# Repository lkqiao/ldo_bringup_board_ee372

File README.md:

# ldo_bringup_board_ee372

LDO bring up PCB for EE372.

- 20 µF / 390 mΩ RC dominant pole compensation at VOUT
- 0.1 µF cap at the NR pin for bandgap reference noise filtering
- Switch on the MD pin to toggle between high power and low power modes

## Project libraries

Both libraries are registered in the project-local `sym-lib-table` /
`fp-lib-table` under the nickname `ldo_bringup_board_ee372`, via
`${KIPRJMOD}`, so they resolve on any clone without per-machine setup.

| File | Contents |
|------|----------|
| `ldo_bringup_board_ee372.kicad_sym` | `LDO_DualMode_BGR_EE372` — 32-pin symbol + EP |
| `ldo_bringup_board_ee372.pretty/` | `QFN-32-1EP_7x7mm_P0.65mm_EP5.1x5.1mm_QuikPak` |

### Package

Quik-Pak **QP-QFN32-7MM-.65MM**, open-cavity QFN-32, rev A2. The numbers
come from the EE372B PCB Design Guidelines (Fall 2026, section 2), the
Quik-Pak mechanical drawing `QP-QFN7X7-32-650 PACKAGE.pdf` and the bonding
drawing `QP-QFN7X7-32-650 BONDING.dwg`.

| Parameter | Value | Source |
|---|---|---|
| Body | 7.000 x 7.000 mm, 0.800 tall | guidelines 2.1, package drawing |
| Leads | 32 (8/side), pitch 0.650 mm | guidelines 2.1, package drawing |
| Lead width x length | 0.300 x 0.380 mm | package drawing, bottom view |
| Lead-centre span per side | 4.550 mm | package drawing, bottom view |
| Exposed paddle (bottom) | 5.100 x 5.100 mm | package drawing, bottom view |
| Die attach surface (in the cavity) | 5.300 x 5.300 mm | bonding drawing note 3; not the land size |
| Pin-1 ID | 0.400 x 45 deg chamfer | package drawing, top view |

### Footprint

`QFN-32-1EP_7x7mm_P0.65mm_EP5.1x5.1mm_QuikPak`, checked against every
requirement in guidelines section 2.2.

| Pad size | Pitch | EP land | Courtyard |
|---|---|---|---|
| 0.30 x 0.85 mm | 0.65 mm | 5.10 x 5.10 mm | 8.26 x 8.26 mm |

- Lands extend 0.375 mm past the body edge and sit 0.475 mm from the EP land.
- 9 thermal vias, 0.3 mm drill, numbered 33 with the EP. They are tented on
  both sides because the EP has no full mask opening. Instead, 16 mask windows
  sit exactly over the 16 paste windows.
- EP paste is a 4x4 window pane at 52.5% coverage.
- Pin 1 is marked on silkscreen with a dot and a 0.4 mm chamfered corner.
- The 3D model is KiCad's stock `QFN-32-1EP_7x7mm_P0.65mm_EP5.46x5.46mm.step`,
  0.9 mm tall with a closed top. It is only for renders.

### Pinout

From the die pad map. Package pin 1 = the first pad down the **left** side,
i.e. the die orientation mark aligned to the package `PIN #1 ID`. Numbering
then runs CCW: left T→B (1-8), bottom L→R (9-16), right B→T (17-24),
top R→L (25-32). Pin 33 is the exposed pad.

| | | | |
|---|---|---|---|
| 1 VSS | 9 VDD | 17 VSS | 25 VDD |
| 2 VSS | 10 VSS | 18 VSS | 26 VDD |
| 3 VSS | 11 VSS | 19 VSS | 27 VDD |
| 4 VDD | 12 VSS | 20 VSS | 28 VSS |
| 5 IBIAS | 13 VSS | 21 VOUT | 29 MD |
| 6 VSS | 14 VSS | 22 VOUT | 30 NR |
| 7 VSS | 15 VSS | 23 VSS | 31 VSS |
| 8 VDD | 16 VDD | 24 VDD | 32 VDD |

Census: 18 × VSS, 9 × VDD, 2 × VOUT, 1 × MD, 1 × NR, 1 × IBIAS = 32.

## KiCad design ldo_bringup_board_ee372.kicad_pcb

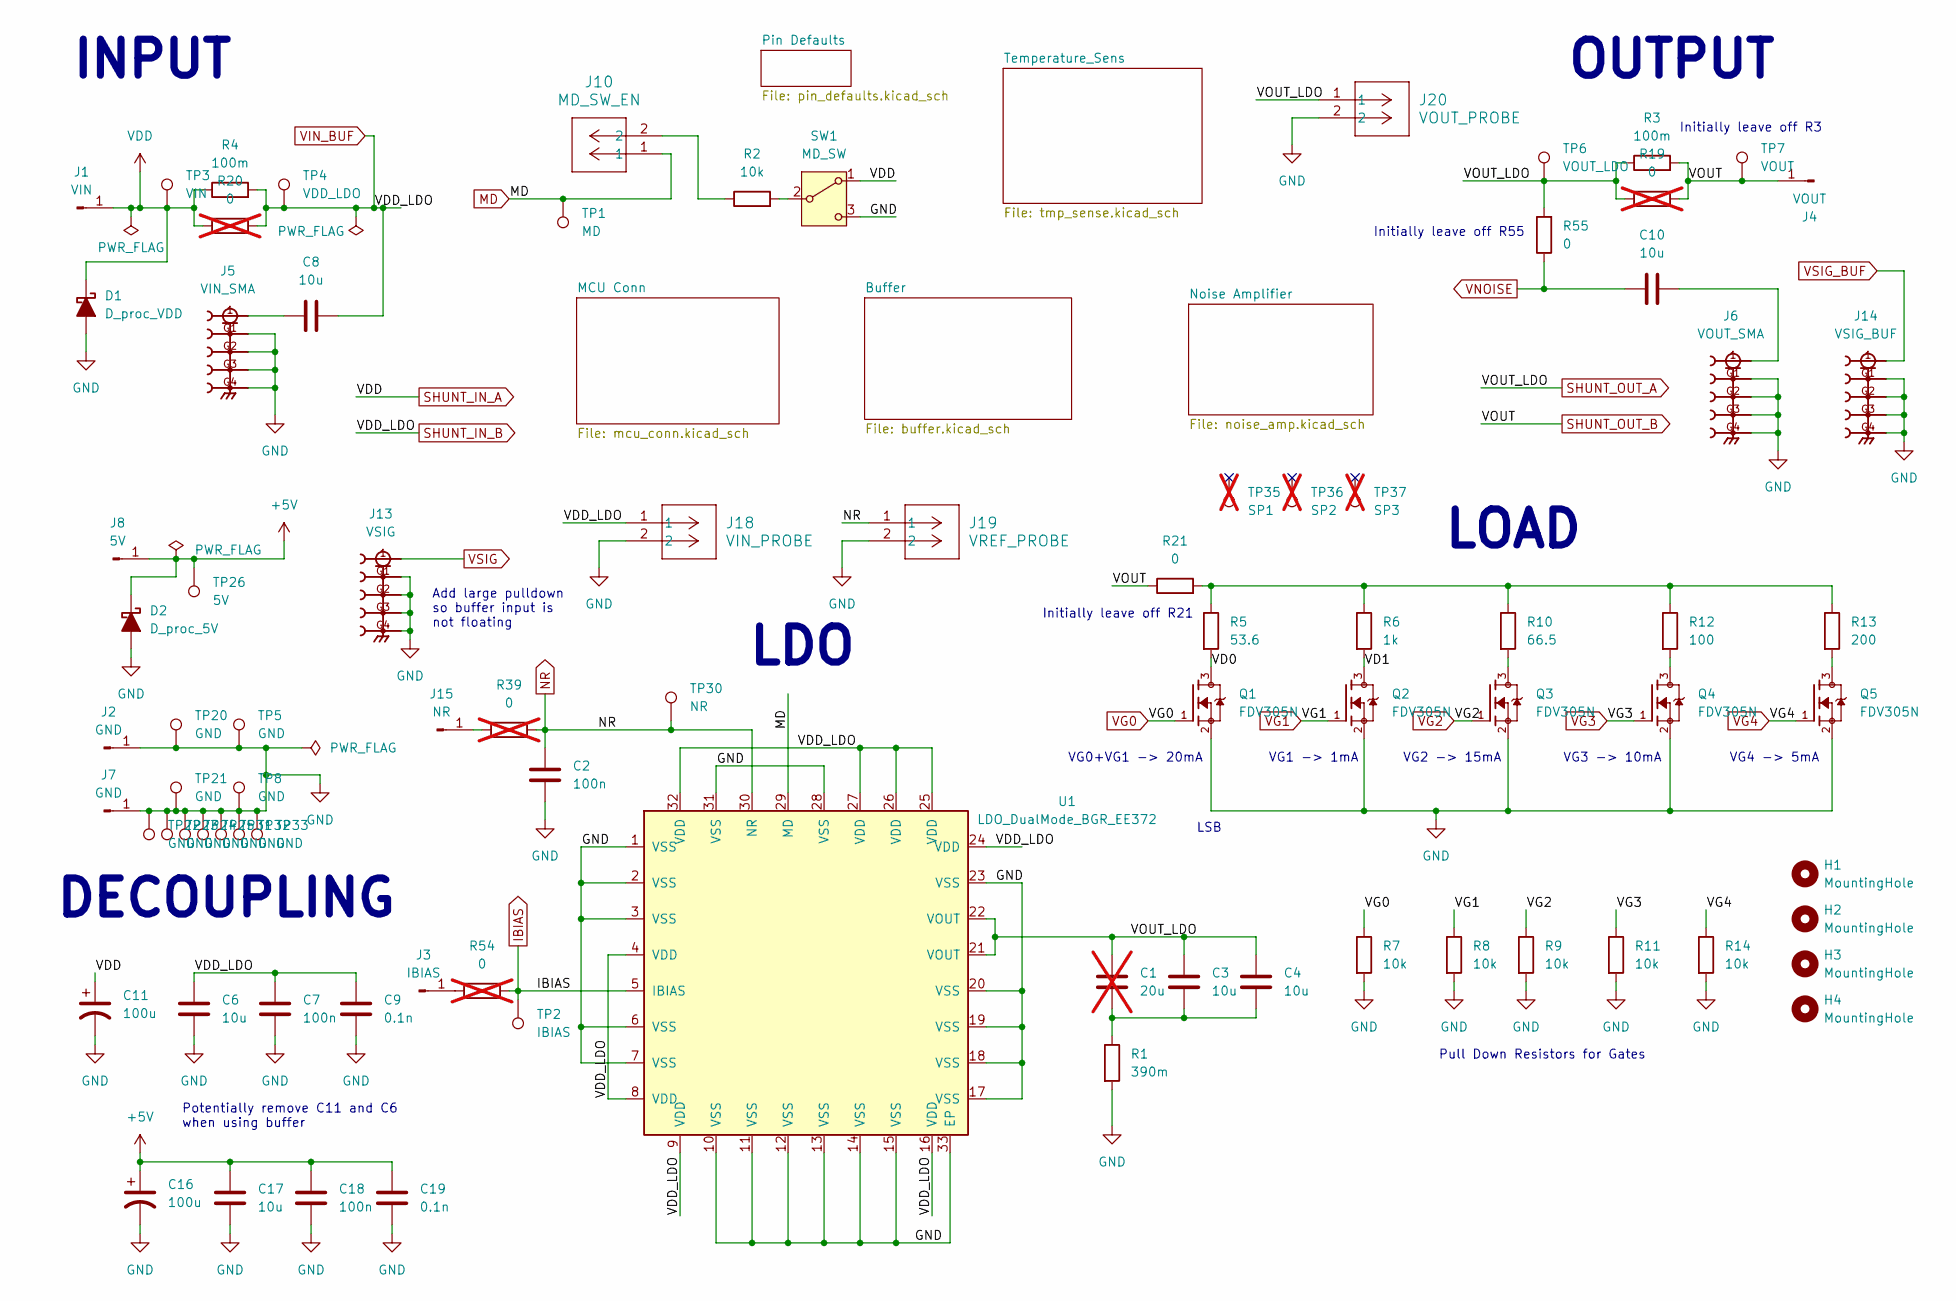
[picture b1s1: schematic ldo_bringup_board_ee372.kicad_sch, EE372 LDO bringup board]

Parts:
C1: 20u; C_1812_4532Metric_Pad1.57x3.40mm_HandSolder; Manufacturer Part Number C1812C206K3RLCTU; not fitted
C2, C7, C18: 100n; C_0805_2012Metric_Pad1.18x1.45mm_HandSolder; Manufacturer Part Number CL21B104KBCNNNC
C3, C4: 10u; C_1206_3216Metric_Pad1.33x1.80mm_HandSolder; Manufacturer Part Number C1206C106J3RACAUTO
C6, C8, C10, C17: 10u; C_1206_3216Metric_Pad1.33x1.80mm_HandSolder; Manufacturer Part Number GRM319R61E106KA12D
C9, C19: 0.1n; C_0805_2012Metric_Pad1.18x1.45mm_HandSolder; Manufacturer Part Number CL21C101JBANNNC
C11, C16: 100u; CP_Radial_D6.3mm_P2.50mm; Manufacturer Part Number EEU-FC1E101S
D1: D_proc_VDD; D_SMA_Handsoldering; Manufacturer Part Number B120-13-F
D2: D_proc_5V; D_SMA_Handsoldering; Manufacturer Part Number B120-13-F
H1, H2, H3, H4: MountingHole; MountingHole_3.2mm_M3
J1: VIN; CalTest_CT3151SP; Manufacturer Part Number CT3151SP-2
J2, J7: GND; CalTest_CT3151SP; Manufacturer Part Number CT3151SP-0
J3: IBIAS; CalTest_CT3151SP; Manufacturer Part Number CT3151SP-9
J4: VOUT; CalTest_CT3151SP; Manufacturer Part Number CT3151SP-4
J5: VIN_SMA; SMA_Samtec_SMA-J-P-H-ST-EM1_EdgeMount_G; Manufacturer Part Number SMA-J-P-H-ST-EM1
J6: VOUT_SMA; SMA_Samtec_SMA-J-P-H-ST-EM1_EdgeMount_G; Manufacturer Part Number SMA-J-P-H-ST-EM1
J8: 5V; CalTest_CT3151SP; Manufacturer Part Number CT3151SP-2
J10: MD_SW_EN; CONN_PxC02S_SUL; Manufacturer Part Number PEC02SAAN
J13: VSIG; SMA_Samtec_SMA-J-P-H-ST-EM1_EdgeMount_G; Manufacturer Part Number SMA-J-P-H-ST-EM1
J14: VSIG_BUF; SMA_Samtec_SMA-J-P-H-ST-EM1_EdgeMount_G; Manufacturer Part Number SMA-J-P-H-ST-EM1
J15: NR; CalTest_CT3151SP; Manufacturer Part Number CT3151SP-2
J18: VIN_PROBE; CONN_PxC02S_SUL; Manufacturer Part Number PEC02SAAN
J19: VREF_PROBE; CONN_PxC02S_SUL; Manufacturer Part Number PEC02SAAN
J20: VOUT_PROBE; CONN_PxC02S_SUL; Manufacturer Part Number PEC02SAAN
Q1, Q2, Q3, Q4, Q5: FDV305N; SOT95P240X111-3N; Manufacturer Part Number FDV305N
R1: 390m; R_0805_2012Metric_Pad1.20x1.40mm_HandSolder; Manufacturer Part Number ERJ-6BQFR39V
R2, R7, R8, R9, R11, R14: 10k; R_0805_2012Metric_Pad1.20x1.40mm_HandSolder; Manufacturer Part Number RC0805FR-0710KL
R3, R4: 100m; R_0805_2012Metric_Pad1.20x1.40mm_HandSolder; Manufacturer Part Number ERJ-6DSFR10V
R5: 53.6; R_0805_2012Metric_Pad1.20x1.40mm_HandSolder; Manufacturer Part Number RC0805FR-0753R6L
R6: 1k; R_0805_2012Metric_Pad1.20x1.40mm_HandSolder; Manufacturer Part Number RC0805FR-071KL
R10: 66.5; R_0805_2012Metric_Pad1.20x1.40mm_HandSolder; Manufacturer Part Number RC0805FR-0766R5L
R12: 100; R_0805_2012Metric_Pad1.20x1.40mm_HandSolder; Manufacturer Part Number RC0805FR-07100RL
R13: 200; R_0805_2012Metric_Pad1.20x1.40mm_HandSolder; Manufacturer Part Number RC0805FR-07200RL
R19, R20, R39, R54: 0; R_0805_2012Metric_Pad1.20x1.40mm_HandSolder; Manufacturer Part Number CRCW08050000Z0EAHP; not fitted
R21, R55: 0; R_0805_2012Metric_Pad1.20x1.40mm_HandSolder; Manufacturer Part Number CRCW08050000Z0EAHP
SW1: MD_SW; SW_SPDT_CK_JS102011SAQN; Manufacturer Part Number JS102011SAQN
TP1: MD; TestPoint_Keystone_5005-5009_Compact; Manufacturer Part Number 5005
TP2: IBIAS; TestPoint_Keystone_5005-5009_Compact; Manufacturer Part Number 5005
TP3: VIN; TestPoint_Keystone_5005-5009_Compact; Manufacturer Part Number 5005
TP4: VDD_LDO; TestPoint_Keystone_5005-5009_Compact; Manufacturer Part Number 5005
TP5, TP8, TP20, TP21, TP22, TP23, TP24, TP25, TP31, TP32, TP33: GND; TestPoint_Keystone_5005-5009_Compact; Manufacturer Part Number 5006
TP6: VOUT_LDO; TestPoint_Keystone_5005-5009_Compact; Manufacturer Part Number 5005
TP7: VOUT; TestPoint_Keystone_5005-5009_Compact; Manufacturer Part Number 5005
TP26: 5V; TestPoint_Keystone_5005-5009_Compact; Manufacturer Part Number 5005
TP30: NR; TestPoint_Keystone_5005-5009_Compact; Manufacturer Part Number 5005
TP35: SP1; TestPoint_Keystone_5005-5009_Compact; Manufacturer Part Number 5006; not fitted
TP36: SP2; TestPoint_Keystone_5005-5009_Compact; Manufacturer Part Number 5006; not fitted
TP37: SP3; TestPoint_Keystone_5005-5009_Compact; Manufacturer Part Number 5006; not fitted
U1: LDO_DualMode_BGR_EE372; QFN-32-1EP_7x7mm_P0.65mm_EP5.1x5.1mm_QuikPak

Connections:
+5V: C16.1, C17.1, C18.1, C19.1, D2.1 (K), J8.1 (Pin_1_1), TP26.1 (1_1); also elsewhere on the board
/VD0: Q1.3, R5.2
/VD1: Q2.3, R6.2
GND: C2.2, C6.2, C7.2, C9.2, C11.2, C16.2, C17.2, C18.2, C19.2, D1.2 (A), D2.2 (A), J2.1 (Pin_1_1), J5.G1, J5.G2, J5.G3, J5.G4, J6.G1, J6.G2, J6.G3, J6.G4, J7.1 (Pin_1_1), J13.G1, J13.G2, J13.G3, J13.G4, J14.G1, J14.G2, J14.G3, J14.G4, J18.2, J19.2, J20.2, Q1.2, Q2.2, Q3.2, Q4.2, Q5.2, R1.2, R7.2, R8.2, R9.2, R11.2, R14.2, SW1.3 (C), TP5.1 (1_1), TP8.1 (1_1), TP20.1 (1_1), TP21.1 (1_1), TP22.1 (1_1), TP23.1 (1_1), TP24.1 (1_1), TP25.1 (1_1), TP31.1 (1_1), TP32.1 (1_1), TP33.1 (1_1), U1.1 (VSS), U1.2 (VSS), U1.3 (VSS), U1.6 (VSS), U1.7 (VSS), U1.10 (VSS), U1.11 (VSS), U1.12 (VSS), U1.13 (VSS), U1.14 (VSS), U1.15 (VSS), U1.17 (VSS), U1.18 (VSS), U1.19 (VSS), U1.20 (VSS), U1.23 (VSS), U1.28 (VSS), U1.31 (VSS), U1.33 (EP); also elsewhere on the board
IBIAS: R54.2, TP2.1 (1_1), U1.5 (IBIAS); also elsewhere on the board
MD: J10.1, TP1.1 (1_1), U1.29 (MD); also elsewhere on the board
NR: C2.1, J19.1, R39.2, TP30.1 (1_1), U1.30 (NR); also elsewhere on the board
unnamed: C1.2, C3.2, C4.2, R1.1
unnamed: C8.1, J5.1
unnamed: C10.2, J6.1
unnamed: J3.1 (Pin_1_1), R54.1
unnamed: J10.2, R2.1
unnamed: J15.1 (Pin_1_1), R39.1
unnamed: Q3.3, R10.2
unnamed: Q4.3, R12.2
unnamed: Q5.3, R13.2
unnamed: R5.1, R6.1, R10.1, R12.1, R13.1, R21.2
unnamed: R2.2, SW1.2 (B)
SHUNT_IN_A: C11.1, D1.1 (K), J1.1 (Pin_1_1), R4.1, R20.1, SW1.1 (A), TP3.1 (1_1); also elsewhere on the board
SHUNT_IN_B: C6.1, C7.1, C8.2, C9.1, J18.1, R4.2, R20.2, TP4.1 (1_1), U1.4 (VDD), U1.8 (VDD), U1.9 (VDD), U1.16 (VDD), U1.24 (VDD), U1.25 (VDD), U1.26 (VDD), U1.27 (VDD), U1.32 (VDD); also elsewhere on the board
SHUNT_OUT_A: C1.1, C3.1, C4.1, J20.1, R3.1, R19.1, R55.2, TP6.1 (1_1), U1.21 (VOUT), U1.22 (VOUT); also elsewhere on the board
SHUNT_OUT_B: J4.1 (Pin_1_1), R3.2, R19.2, R21.1, TP7.1 (1_1); also elsewhere on the board
VG0: Q1.1, R7.1; also elsewhere on the board
VG1: Q2.1, R8.1; also elsewhere on the board
VG2: Q3.1, R9.1; also elsewhere on the board
VG3: Q4.1, R11.1; also elsewhere on the board
VG4: Q5.1, R14.1; also elsewhere on the board
VNOISE: C10.1, R55.1; also elsewhere on the board
VSIG: J13.1; also elsewhere on the board
VSIG_BUF: J14.1; also elsewhere on the board

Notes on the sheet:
OUTPUT
Potentially remove C11 and C6 when using buffer
Initially leave off R3
VG0+VG1 -> 20mA
VG3 -> 10mA
LSB
Add large pulldown so buffer input is not floating
Initially leave off R55
Pull Down Resistors for Gates
VG4 -> 5mA
LOAD
VG2 -> 15mA
DECOUPLING
Initially leave off R21
LDO
VG1 -> 1mA
INPUT

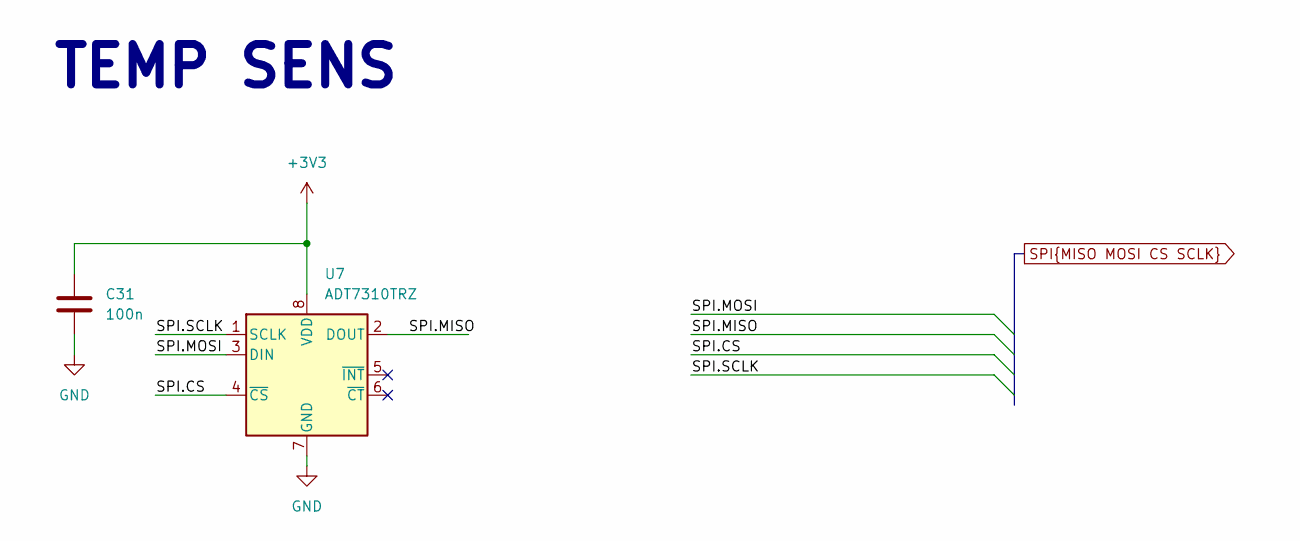
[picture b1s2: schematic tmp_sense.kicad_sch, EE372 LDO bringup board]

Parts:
C31: 100n; C_0805_2012Metric_Pad1.18x1.45mm_HandSolder; Manufacturer Part Number CL21B104KBCNNNC
U7: ADT7310TRZ; SOIC-8_3.9x4.9mm_P1.27mm; Manufacturer Part Number ADT7310TRZ

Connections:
+3V3: C31.1, U7.8 (VDD); also elsewhere on the board
GND: C31.2, U7.7 (GND); also elsewhere on the board
SPI.CS: U7.4 (~CS); also elsewhere on the board
SPI.MISO: U7.2 (DOUT); also elsewhere on the board
SPI.MOSI: U7.3 (DIN); also elsewhere on the board
SPI.SCLK: U7.1 (SCLK); also elsewhere on the board

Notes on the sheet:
TEMP SENS

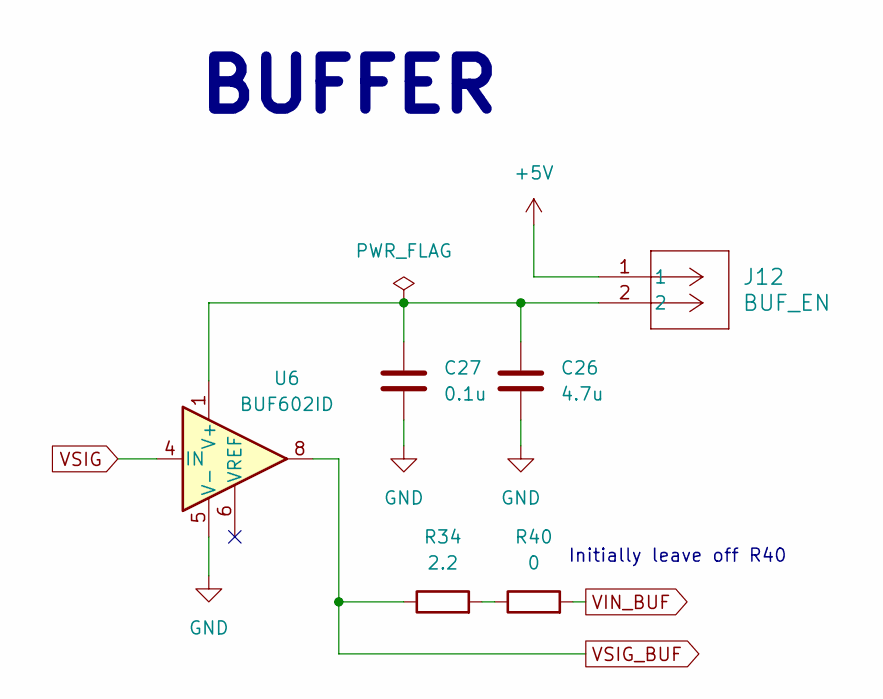
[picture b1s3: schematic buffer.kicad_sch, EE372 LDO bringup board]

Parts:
C26: 4.7u; C_0805_2012Metric_Pad1.18x1.45mm_HandSolder; Manufacturer Part Number CL21B475KAFNNNE
C27: 0.1u; C_0805_2012Metric_Pad1.18x1.45mm_HandSolder; Manufacturer Part Number CL21B104KBCNNNC
J12: BUF_EN; CONN_PxC02S_SUL; Manufacturer Part Number PEC02SAAN
R34: 2.2; R_0603_1608Metric_Pad0.98x0.95mm_HandSolder; Manufacturer Part Number ERJ-3RQF2R2V
R40: 0; R_0603_1608Metric_Pad0.98x0.95mm_HandSolder; Manufacturer Part Number CRCW06030000Z0EAHP
U6: BUF602ID; SOIC-8_3.9x4.9mm_P1.27mm; Manufacturer Part Number BUF602ID

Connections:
+5V: J12.1; also elsewhere on the board
GND: C26.1, C27.1, U6.5 (V-); also elsewhere on the board
unnamed: R34.2, R40.1
unnamed: C26.2, C27.2, J12.2, U6.1 (V+)
SHUNT_IN_B: R40.2; also elsewhere on the board
VSIG: U6.4 (IN); also elsewhere on the board
VSIG_BUF: R34.1, U6.8; also elsewhere on the board

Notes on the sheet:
Initially leave off R40
BUFFER

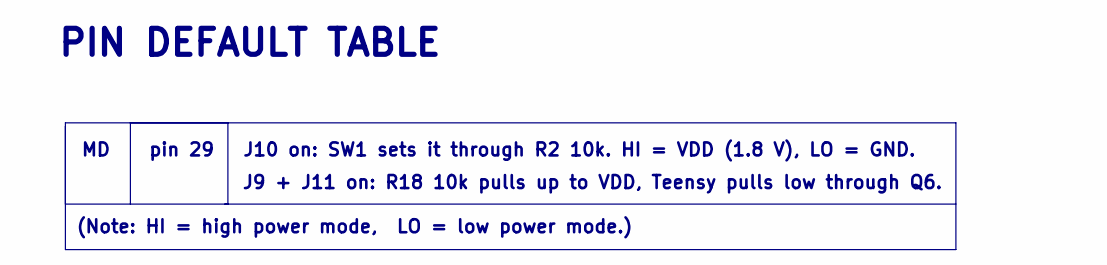
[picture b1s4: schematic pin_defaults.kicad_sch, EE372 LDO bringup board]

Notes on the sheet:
J9 + J11 on: R18 10k pulls up to VDD, Teensy pulls low through Q6.
(Note: HI = high power mode, LO = low power mode.)
PIN DEFAULT TABLE
MD pin 29 J10 on: SW1 sets it through R2 10k. HI = VDD (1.8 V), LO = GND.

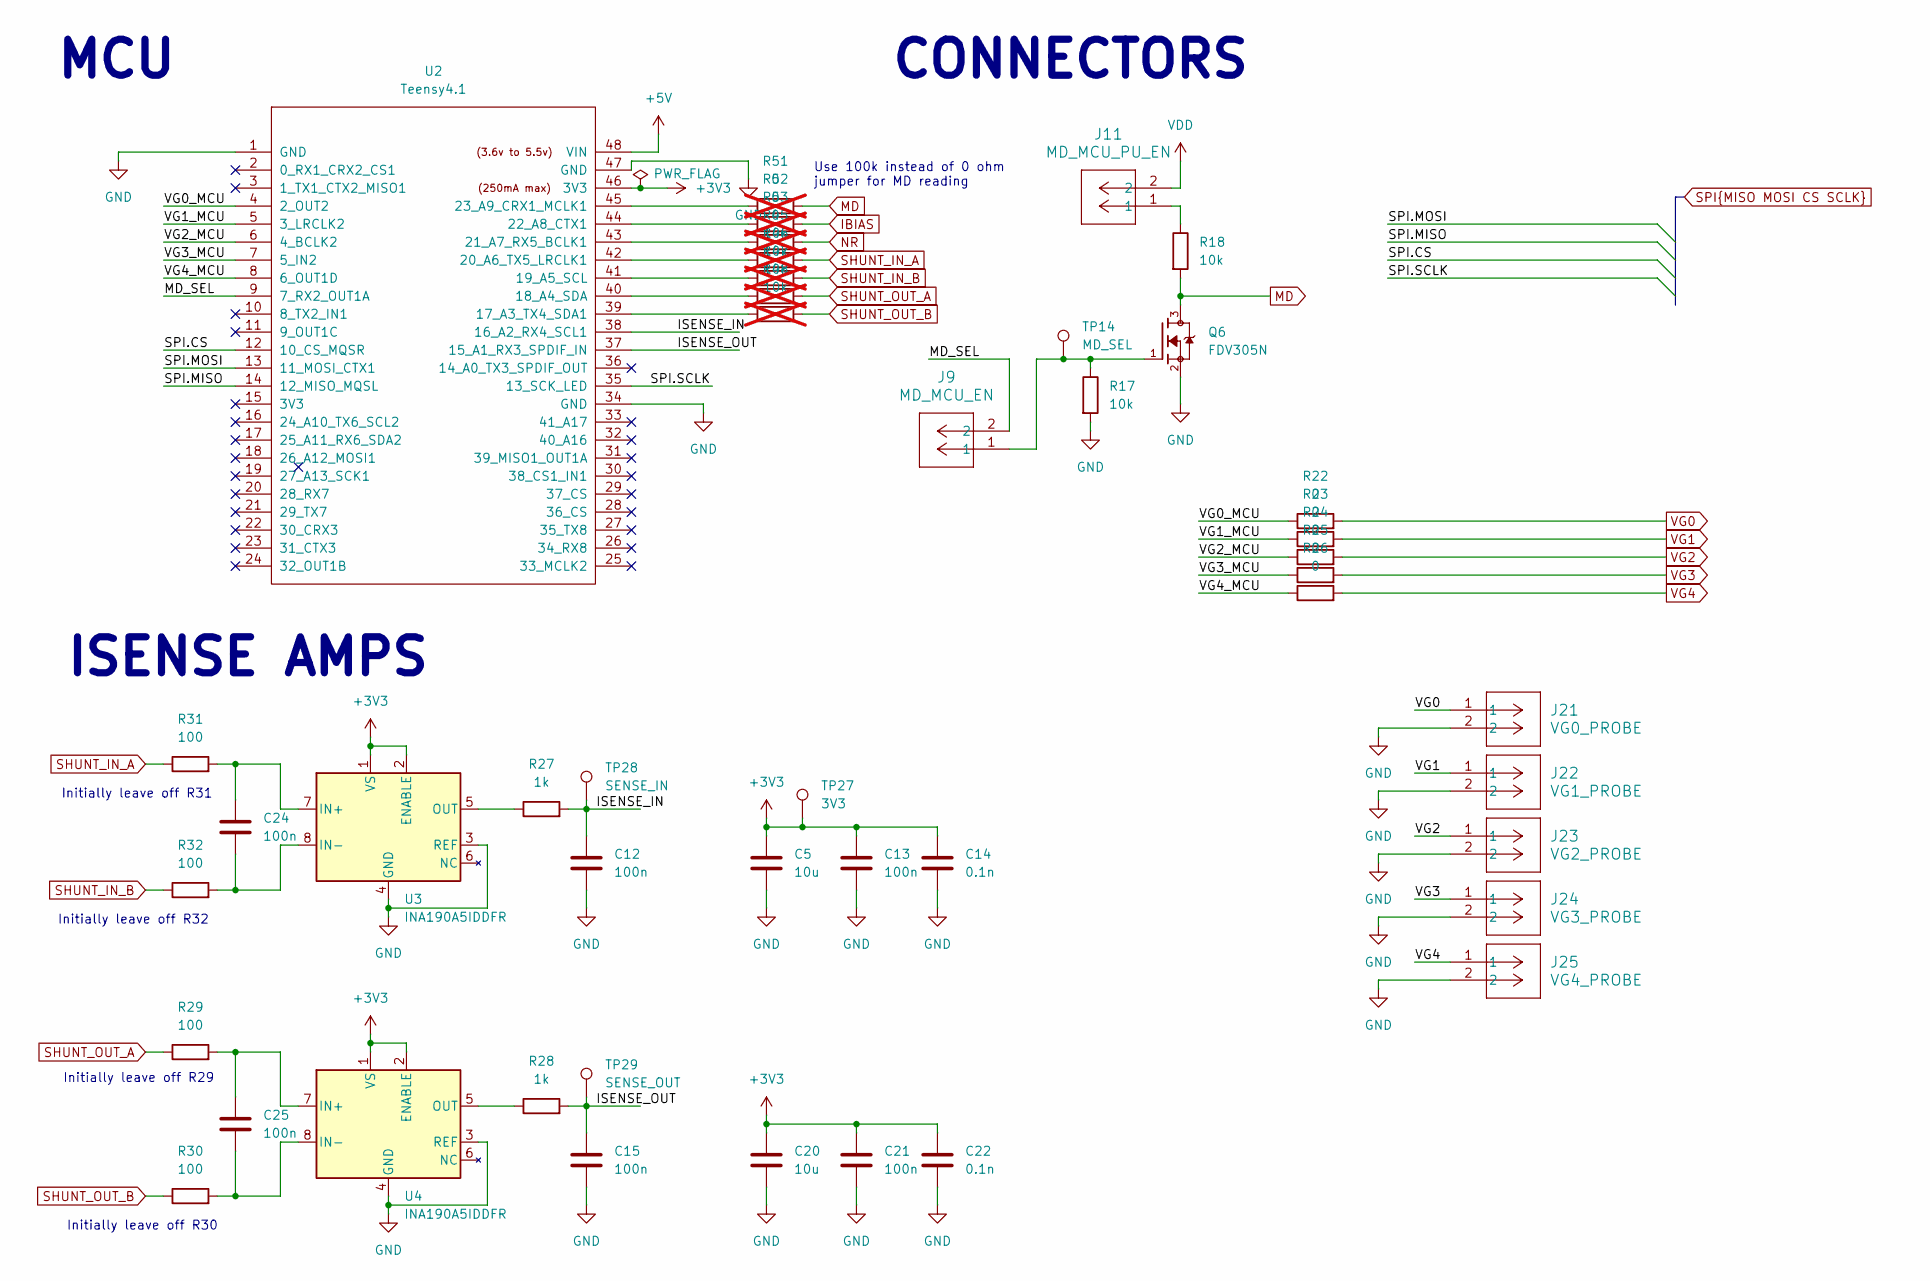
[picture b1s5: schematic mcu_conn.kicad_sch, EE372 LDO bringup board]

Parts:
C5, C20: 10u; C_1206_3216Metric_Pad1.33x1.80mm_HandSolder; Manufacturer Part Number GRM319R61E106KA12D
C12, C13, C15, C21, C24, C25: 100n; C_0805_2012Metric_Pad1.18x1.45mm_HandSolder; Manufacturer Part Number CL21B104KBCNNNC
C14, C22: 0.1n; C_0805_2012Metric_Pad1.18x1.45mm_HandSolder; Manufacturer Part Number CL21C101JBANNNC
J9: MD_MCU_EN; CONN_PxC02S_SUL; Manufacturer Part Number PEC02SAAN
J11: MD_MCU_PU_EN; CONN_PxC02S_SUL; Manufacturer Part Number PEC02SAAN
J21: VG0_PROBE; CONN_PxC02S_SUL; Manufacturer Part Number PEC02SAAN
J22: VG1_PROBE; CONN_PxC02S_SUL; Manufacturer Part Number PEC02SAAN
J23: VG2_PROBE; CONN_PxC02S_SUL; Manufacturer Part Number PEC02SAAN
J24: VG3_PROBE; CONN_PxC02S_SUL; Manufacturer Part Number PEC02SAAN
J25: VG4_PROBE; CONN_PxC02S_SUL; Manufacturer Part Number PEC02SAAN
Q6: FDV305N; SOT95P240X111-3N; Manufacturer Part Number FDV305N
R17, R18: 10k; R_0603_1608Metric_Pad0.98x0.95mm_HandSolder; Manufacturer Part Number RC0603FR-0710KL
R22, R23, R24, R25, R26: 0; R_0603_1608Metric_Pad0.98x0.95mm_HandSolder; Manufacturer Part Number CRCW06030000Z0EAHP
R27, R28: 1k; R_0603_1608Metric_Pad0.98x0.95mm_HandSolder; Manufacturer Part Number RC0603FR-071KL
R29, R30, R31, R32: 100; R_0603_1608Metric_Pad0.98x0.95mm_HandSolder; Manufacturer Part Number ERJ-3EKF1000V
R45, R46, R47, R48: 10k; R_0805_2012Metric_Pad1.20x1.40mm_HandSolder; Manufacturer Part Number RC0805FR-0710KL; not fitted
R51, R52, R53: 0; R_0603_1608Metric_Pad0.98x0.95mm_HandSolder; Manufacturer Part Number CRCW06030000Z0EAHP; not fitted
TP14: MD_SEL; TestPoint_Keystone_5005-5009_Compact; Manufacturer Part Number 5005
TP27: 3V3; TestPoint_Keystone_5005-5009_Compact; Manufacturer Part Number 5005
TP28: SENSE_IN; TestPoint_Keystone_5005-5009_Compact; Manufacturer Part Number 5005
TP29: SENSE_OUT; TestPoint_Keystone_5005-5009_Compact; Manufacturer Part Number 5005
U2: Teensy4.1; Teensy41_Sockets
U3, U4: INA190A5IDDFR; TSOT-23-8_HandSoldering; Manufacturer Part Number INA190A5IDDFR

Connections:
+3V3: C5.1, C13.1, C14.1, C20.1, C21.1, C22.1, TP27.1 (1_1), U2.46 (3V3), U3.1 (VS), U3.2 (ENABLE), U4.1 (VS), U4.2 (ENABLE); also elsewhere on the board
+5V: U2.48 (VIN); also elsewhere on the board
/MCU Conn/ISENSE_IN: C12.1, R27.2, TP28.1 (1_1), U2.38 (16_A2_RX4_SCL1)
/MCU Conn/ISENSE_OUT: C15.1, R28.2, TP29.1 (1_1), U2.37 (15_A1_RX3_SPDIF_IN)
/MCU Conn/MD_SEL: J9.2, U2.9 (7_RX2_OUT1A)
/MCU Conn/VG0_MCU: R22.1, U2.4 (2_OUT2)
/MCU Conn/VG1_MCU: R23.1, U2.5 (3_LRCLK2)
/MCU Conn/VG2_MCU: R24.1, U2.6 (4_BCLK2)
/MCU Conn/VG3_MCU: R25.1, U2.7 (5_IN2)
/MCU Conn/VG4_MCU: R26.1, U2.8 (6_OUT1D)
GND: C5.2, C12.2, C13.2, C14.2, C15.2, C20.2, C21.2, C22.2, J21.2, J22.2, J23.2, J24.2, J25.2, Q6.2, R17.2, U2.1 (GND), U2.34 (GND), U2.47 (GND), U3.3 (REF), U3.4 (GND), U4.3 (REF), U4.4 (GND); also elsewhere on the board
IBIAS: R52.2; also elsewhere on the board
MD: Q6.3, R18.2, R51.2; also elsewhere on the board
NR: R53.2; also elsewhere on the board
unnamed: J9.1, Q6.1, R17.1, TP14.1 (1_1)
unnamed: J11.1, R18.1
unnamed: R48.1, U2.39 (17_A3_TX4_SDA1)
unnamed: R47.1, U2.40 (18_A4_SDA)
unnamed: R46.1, U2.41 (19_A5_SCL)
unnamed: R45.1, U2.42 (20_A6_TX5_LRCLK1)
unnamed: R53.1, U2.43 (21_A7_RX5_BCLK1)
unnamed: R52.1, U2.44 (22_A8_CTX1)
unnamed: R51.1, U2.45 (23_A9_CRX1_MCLK1)
unnamed: C24.1, R31.2, U3.7 (IN+)
unnamed: C24.2, R32.2, U3.8 (IN-)
unnamed: R27.1, U3.5 (OUT)
unnamed: C25.1, R29.2, U4.7 (IN+)
unnamed: C25.2, R30.2, U4.8 (IN-)
unnamed: R28.1, U4.5 (OUT)
SHUNT_IN_A: J11.2, R31.1, R45.2; also elsewhere on the board
SHUNT_IN_B: R32.1, R46.2; also elsewhere on the board
SHUNT_OUT_A: R29.1, R47.2; also elsewhere on the board
SHUNT_OUT_B: R30.1, R48.2; also elsewhere on the board
SPI.CS: U2.12 (10_CS_MQSR); also elsewhere on the board
SPI.MISO: U2.14 (12_MISO_MQSL); also elsewhere on the board
SPI.MOSI: U2.13 (11_MOSI_CTX1); also elsewhere on the board
SPI.SCLK: U2.35 (13_SCK_LED); also elsewhere on the board
VG0: J21.1, R22.2; also elsewhere on the board
VG1: J22.1, R23.2; also elsewhere on the board
VG2: J23.1, R24.2; also elsewhere on the board
VG3: J24.1, R25.2; also elsewhere on the board
VG4: J25.1, R26.2; also elsewhere on the board

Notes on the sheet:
CONNECTORS
MCU
Use 100k instead of 0 ohm jumper for MD reading
Initially leave off R29
ISENSE AMPS
Initially leave off R32
Initially leave off R30
Initially leave off R31

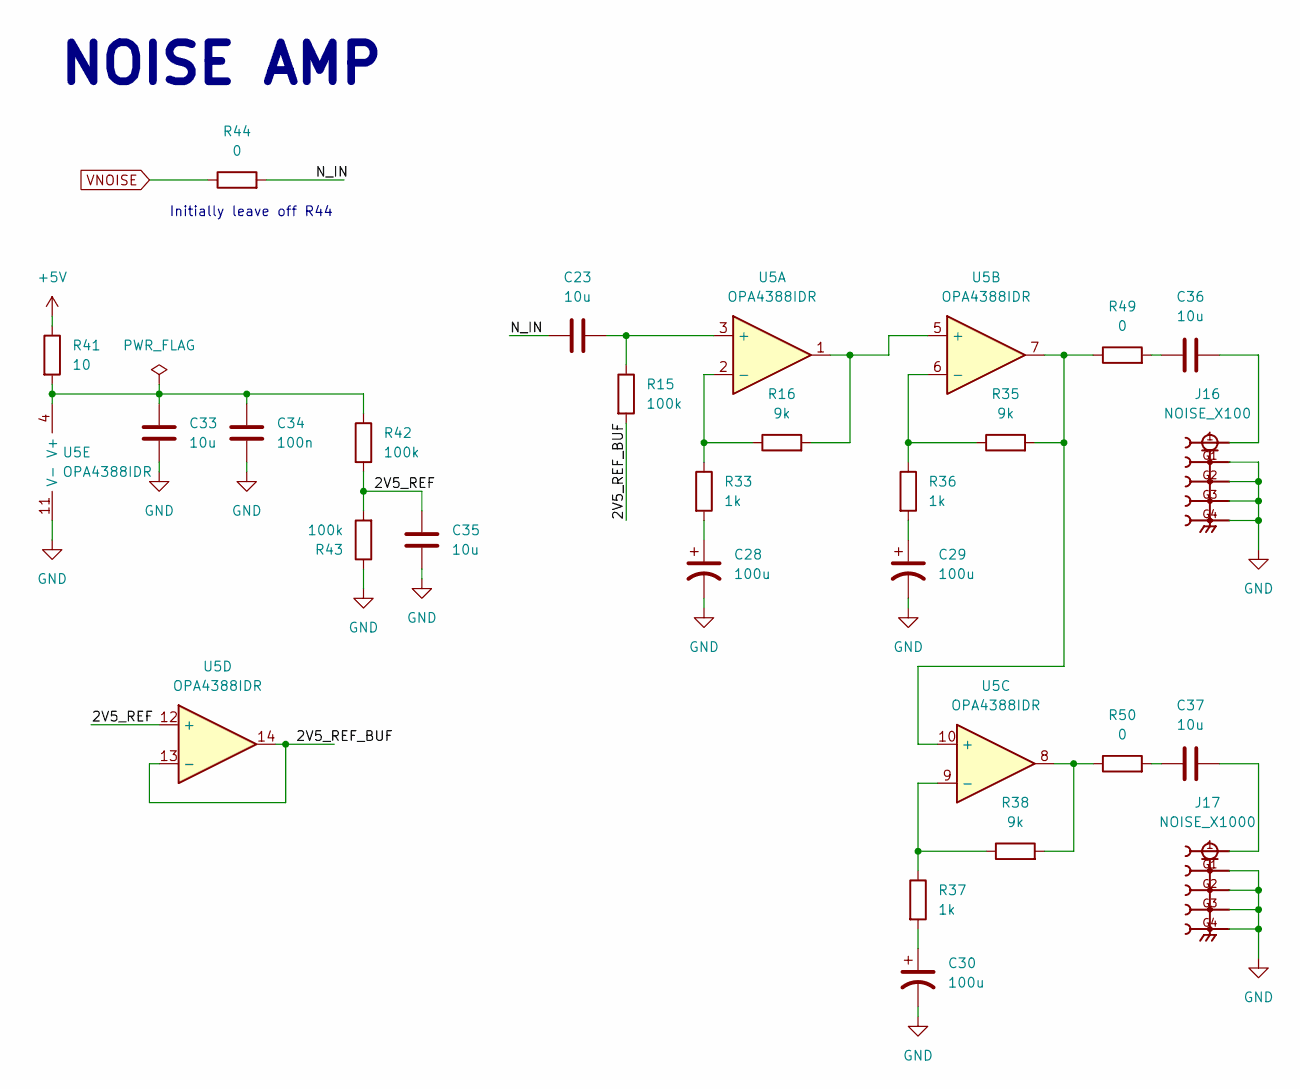
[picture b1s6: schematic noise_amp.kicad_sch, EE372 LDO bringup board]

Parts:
C23, C33, C35, C36, C37: 10u; C_1206_3216Metric_Pad1.33x1.80mm_HandSolder; Manufacturer Part Number GRM319R61E106KA12D
C28, C29, C30: 100u; CP_Radial_D6.3mm_P2.50mm; Manufacturer Part Number EEU-FC1E101S
C34: 100n; C_0805_2012Metric_Pad1.18x1.45mm_HandSolder; Manufacturer Part Number CL21B104KBCNNNC
J16: NOISE_X100; SMA_Samtec_SMA-J-P-H-ST-EM1_EdgeMount_G; Manufacturer Part Number SMA-J-P-H-ST-EM1
J17: NOISE_X1000; SMA_Samtec_SMA-J-P-H-ST-EM1_EdgeMount_G; Manufacturer Part Number SMA-J-P-H-ST-EM1
R15, R42, R43: 100k; R_0603_1608Metric_Pad0.98x0.95mm_HandSolder; Manufacturer Part Number RC0603FR-07100KL
R16, R35, R38: 9k; R_0805_2012Metric_Pad1.20x1.40mm_HandSolder; Manufacturer Part Number RT0805BRE079KL
R33, R36, R37: 1k; R_0603_1608Metric_Pad0.98x0.95mm_HandSolder; Manufacturer Part Number RC0603FR-071KL
R41: 10; R_0603_1608Metric_Pad0.98x0.95mm_HandSolder; Manufacturer Part Number ERJ-3EKF10R0V
R44: 0; R_0805_2012Metric_Pad1.20x1.40mm_HandSolder; Manufacturer Part Number CRCW08050000Z0EAHP
R49, R50: 0; R_0603_1608Metric_Pad0.98x0.95mm_HandSolder; Manufacturer Part Number CRCW06030000Z0EAHP
U5: OPA4388IDR; SOIC-14_3.9x8.7mm_P1.27mm; Manufacturer Part Number OPA4388IDR

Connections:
+5V: R41.1; also elsewhere on the board
/Noise Amplifier/2V5_REF: C35.1, R42.2, R43.2, U5.12 (+)
/Noise Amplifier/2V5_REF_BUF: R15.2, U5.13 (-), U5.14
/Noise Amplifier/N_IN: C23.2, R44.2
GND: C28.2, C29.2, C30.2, C33.2, C34.2, C35.2, J16.G1, J16.G2, J16.G3, J16.G4, J17.G1, J17.G2, J17.G3, J17.G4, R43.1, U5.11 (V-); also elsewhere on the board
unnamed: C28.1, R33.2
unnamed: C29.1, R36.2
unnamed: C30.1, R37.2
unnamed: C36.1, R49.2
unnamed: C36.2, J16.1
unnamed: C37.1, R50.2
unnamed: C37.2, J17.1
unnamed: R38.2, R50.1, U5.8
unnamed: C23.1, R15.1, U5.3 (+)
unnamed: R16.1, R33.1, U5.2 (-)
unnamed: R16.2, U5.1, U5.5 (+)
unnamed: R35.1, R36.1, U5.6 (-)
unnamed: R35.2, R49.1, U5.7, U5.10 (+)
unnamed: R37.1, R38.1, U5.9 (-)
unnamed: C33.1, C34.1, R41.2, R42.1, U5.4 (V+)
VNOISE: R44.1; also elsewhere on the board

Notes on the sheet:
NOISE AMP
Initially leave off R44

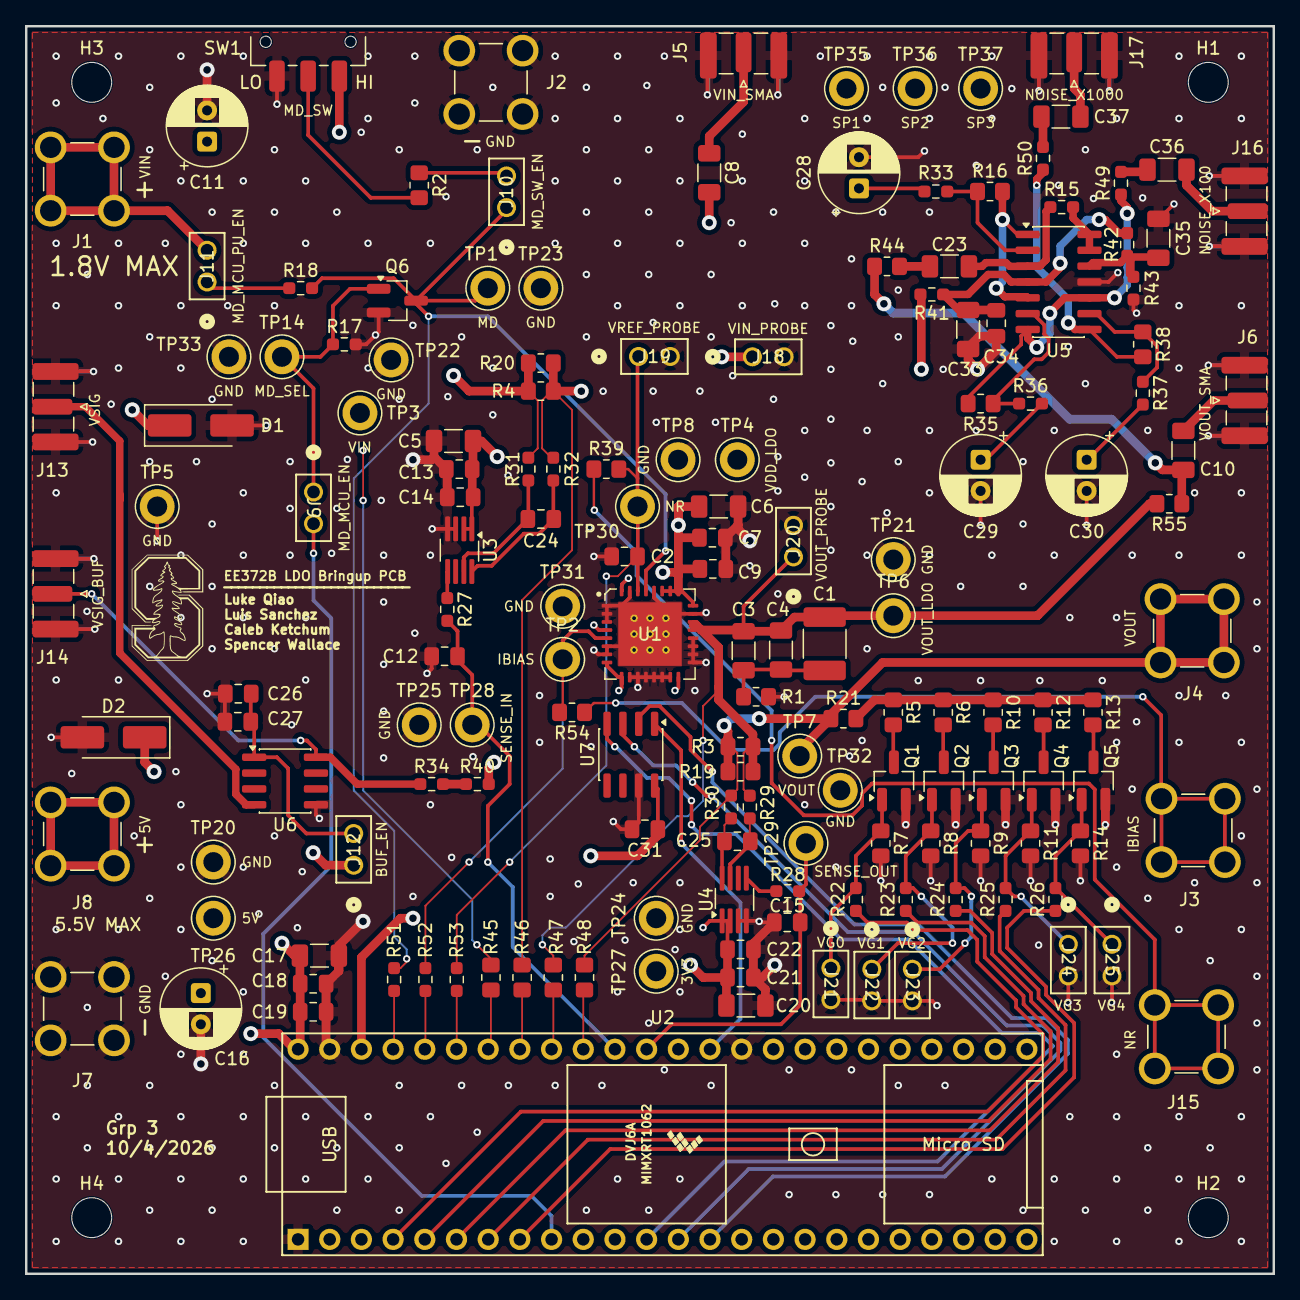
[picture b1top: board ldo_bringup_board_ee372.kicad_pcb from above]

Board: 4 copper layers, 100.0 x 100.0 mm, 162 parts (0 on the bottom side), 78 nets.

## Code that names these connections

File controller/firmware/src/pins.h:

#pragma once
#include <Arduino.h>

// Pin map from the netlist of the EE372B bring-up board (U2, Teensy 4.1).

// Outputs. None of these reach a chip pin.
constexpr uint8_t PIN_VG[5] = {2, 3, 4, 5, 6};  // VG0..VG4 through R22..R26 to Q1..Q5 gates
constexpr uint8_t PIN_MD_SEL = 7;               // Q6 gate through J9; high pulls MD low
constexpr uint8_t ADT_CS = 10;              // ADT7310 CS

// SPI bus to the ADT7310, run by the SPI library.
constexpr uint8_t ADT_MOSI = 11;
constexpr uint8_t ADT_MISO = 12;
constexpr uint8_t ADT_SCK = 13;

// Read-only analog pins. Set to INPUT_DISABLE once in setup() and never changed.
constexpr uint8_t PIN_ISENSE_OUT = 15;  // A1, U4 output, current through R3
constexpr uint8_t PIN_ISENSE_IN = 16;   // A2, U3 output, current through R4
constexpr uint8_t PIN_VOUT_B = 17;      // A3, R48 to SHUNT_OUT_B (VOUT after R3)
constexpr uint8_t PIN_VOUT_LDO = 18;    // A4, R47 to SHUNT_OUT_A (VOUT_LDO)
constexpr uint8_t PIN_VDD_LDO = 19;     // A5, R46 to SHUNT_IN_B (VDD_LDO)
constexpr uint8_t PIN_VDD_A = 20;       // A6, R45 to SHUNT_IN_A (VDD at J1)
constexpr uint8_t PIN_MD = 23;          // A9, R51 to MD

constexpr uint8_t READ_PINS[7] = {PIN_ISENSE_OUT, PIN_ISENSE_IN, PIN_VOUT_B, PIN_VOUT_LDO,
                                  PIN_VDD_LDO,    PIN_VDD_A,     PIN_MD};
constexpr uint8_t DRIVEN_PINS[10] = {PIN_VG[0],  PIN_VG[1],    PIN_VG[2],    PIN_VG[3],   PIN_VG[4],
                                     PIN_MD_SEL, ADT_CS, ADT_MOSI, ADT_MISO, ADT_SCK};

constexpr bool pinsOverlap() {
  for (uint8_t r : READ_PINS)
    for (uint8_t d : DRIVEN_PINS)
      if (r == d) return true;
  return false;
}
static_assert(!pinsOverlap(), "a read pin is also a driven pin");
